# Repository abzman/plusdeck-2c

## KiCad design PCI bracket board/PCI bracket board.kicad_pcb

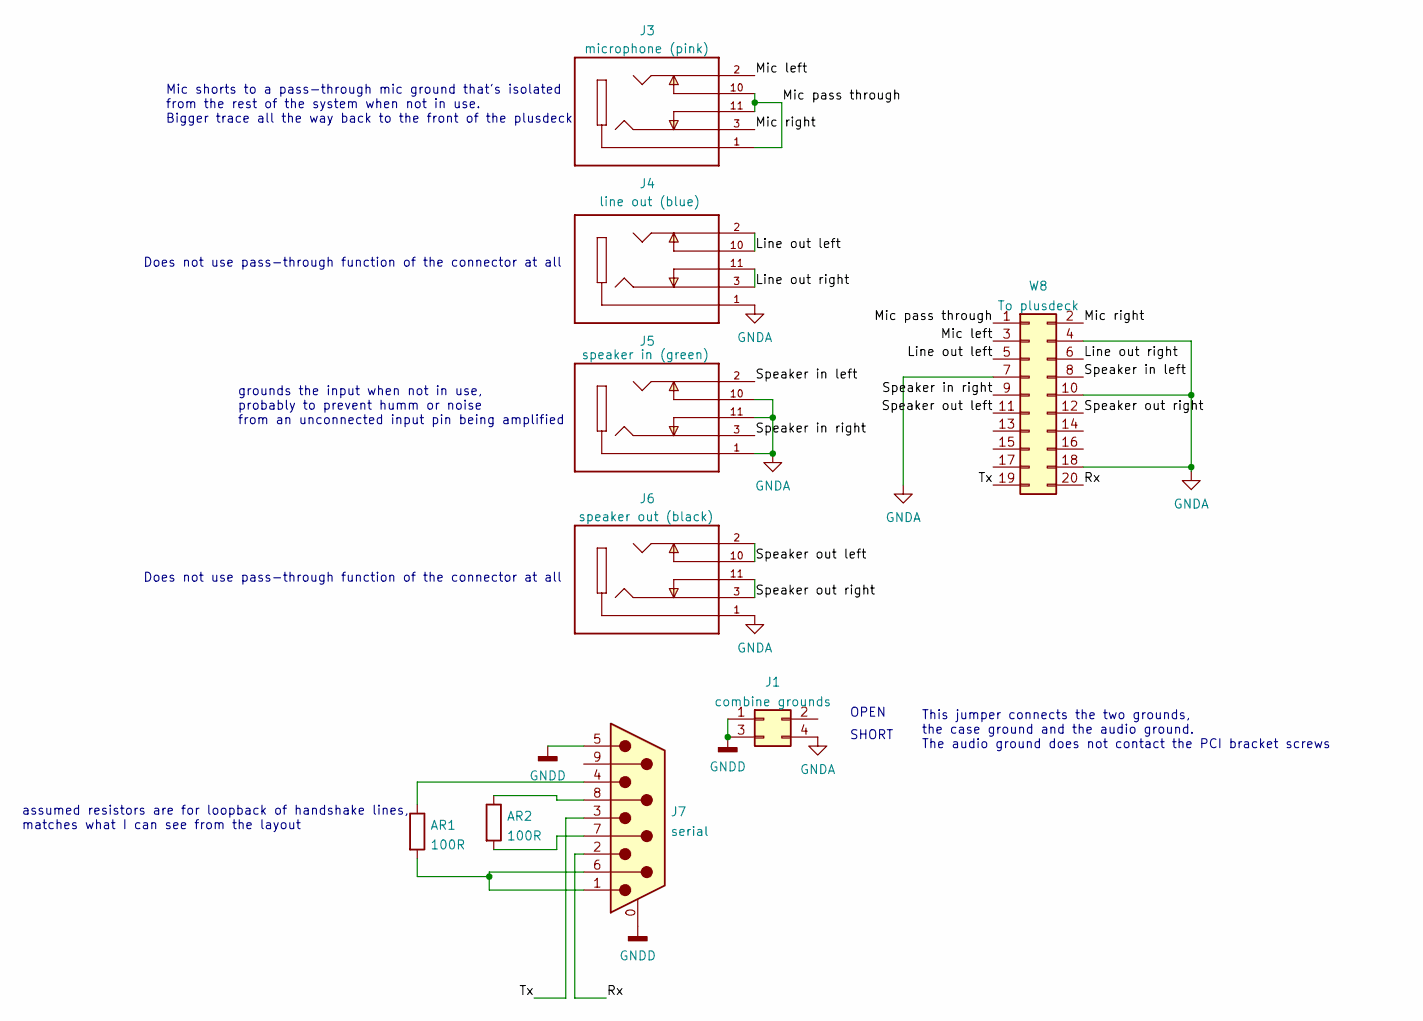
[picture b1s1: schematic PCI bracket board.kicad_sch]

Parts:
AR1, AR2: 100R; R_Axial_DIN0207_L6.3mm_D2.5mm_P10.16mm_Horizontal
J1: combine grounds; PinHeader_2x02_P2.54mm_Vertical
J3: microphone (pink); CUI_SJ1-3525N; PARTREV 1.02
J4: line out (blue); CUI_SJ1-3525N; PARTREV 1.02
J5: speaker in (green); CUI_SJ1-3525N; PARTREV 1.02
J6: speaker out (black); CUI_SJ1-3525N; PARTREV 1.02
J7: serial; DSUB-9_Male_Horizontal_P2.77x2.84mm_EdgePinOffset7.70mm_Hou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
W8: To plusdeck; PinHeader_2x10_P2.54mm_Horizontal

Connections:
/Line out left: J4.2, J4.10, W8.5
/Line out right: J4.3, J4.11, W8.6
/Mic left: J3.2, W8.3
/Mic pass through: J3.1, J3.10, J3.11, W8.1
/Mic right: J3.3, W8.2
/Rx: J7.2, W8.20
/Speaker in left: J5.2, W8.8
/Speaker in right: J5.3, W8.9
/Speaker out left: J6.2, J6.10, W8.11
/Speaker out right: J6.3, J6.11, W8.12
/Tx: J7.3, W8.19
GNDA: J1.4, J4.1, J5.1, J5.10, J5.11, J6.1, W8.4, W8.7, W8.10, W8.18
GNDD: J1.1, J1.3, J7.0 (PAD), J7.5
unnamed: AR1.2, J7.1, J7.6
unnamed: AR1.1, J7.4
unnamed: AR2.2, J7.7
unnamed: AR2.1, J7.8

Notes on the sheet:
OPEN
This jumper connects the two grounds, the case ground and the audio ground. The audio ground does not contact the PCI bracket screws
Does not use pass-through function of the connector at all
SHORT
Mic shorts to a pass-through mic ground that's isolated from the rest of the system when not in use. Bigger trace all the way back to the front of the plusdeck
assumed resistors are for loopback of handshake lines, matches what I can see from the layout
grounds the input when not in use, probably to prevent humm or noise from an unconnected input pin being amplified

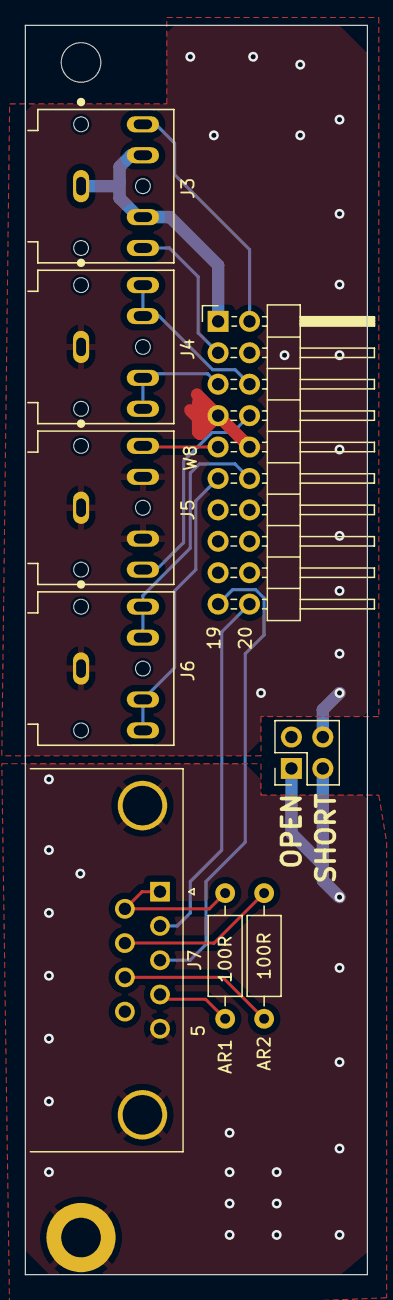
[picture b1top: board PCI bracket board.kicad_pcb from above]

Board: 2 copper layers, 27.7 x 101.0 mm, 9 parts (0 on the bottom side), 17 nets.

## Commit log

2022-02-23 schematic and notes
2022-02-23 added layout
2022-03-14 generated gerbers
2022-03-14 first gerber zip
2022-11-25 added gitignore
2023-11-25 updated copper fill
2023-11-25 updated gerbers
2024-02-04 updates before posting
